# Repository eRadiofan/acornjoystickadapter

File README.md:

Joystick Adapter for Acorn Archimedes Computers
===============================================

KiCad project for an Archimedes joystick adapter. Derived from an initial design by **Ian Haylock** that plugs externally into the computers parallel port and enables two Atari style joysticks to be plugged in. Software must be installed on the Archimedes to recognize the adapter, see ``software`` folder. Full details and pictures can be found in this Stardot Forum [thread](https://stardot.org.uk/forums/viewtopic.php?f=16&t=24492). See ``release`` folder for latest version manufcatoring files along with a BOM file.

This fork contains some improvements by Radiofan, including shorter traces, adjustments for (slightly cheaper) connectors, use of 0805 resistors and through-hole capacitors (common stock).

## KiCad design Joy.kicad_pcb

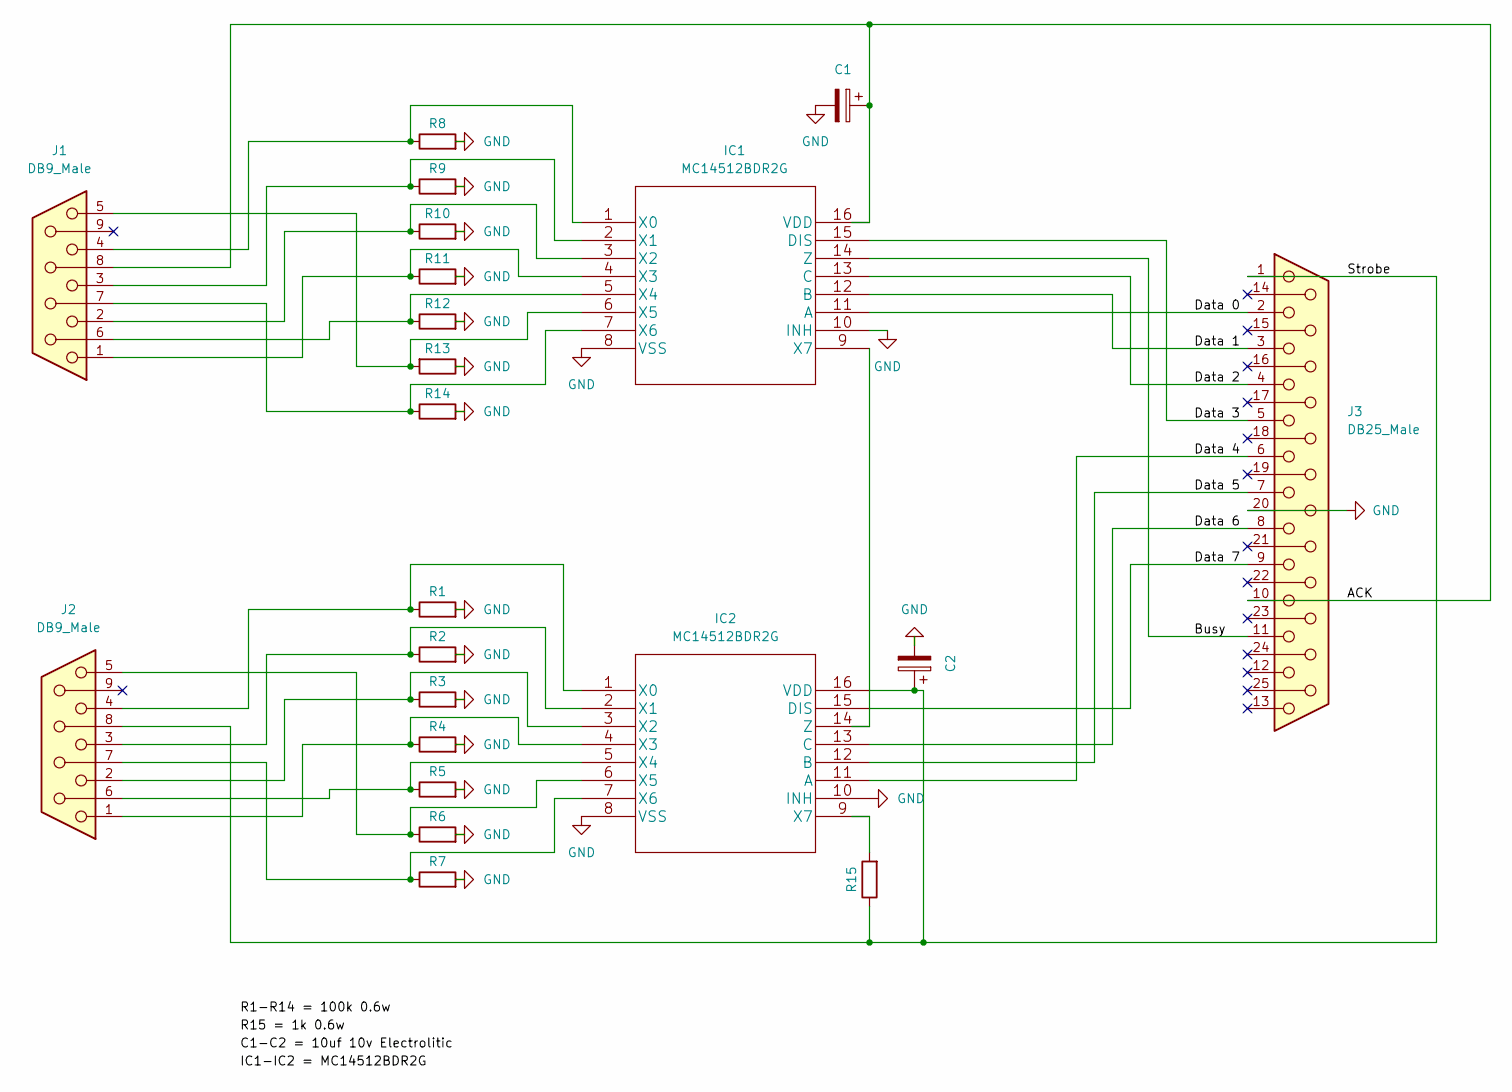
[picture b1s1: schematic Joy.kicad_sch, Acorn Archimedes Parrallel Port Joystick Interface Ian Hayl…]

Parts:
C1, C2: C_Polarized, 10uf Eletrolitic; CP_Radial_D5.0mm_P2.00mm
IC1, IC2: MC14512BDR2G; SOIC-16_3.9x9.9mm_P1.27mm
J1, J2: DB9_Male; 5747840-4
J3: DB25_Male; 5788794-1
R1, R2, R3, R4, R5, R6, R7, R8, R9, R10, R11, R12, R13, R14: 100k; R_0805_2012Metric_Pad1.20x1.40mm_HandSolder
R15: 1k; R_0805_2012Metric_Pad1.20x1.40mm_HandSolder

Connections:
/ACK: C1.1, IC1.16 (VDD), J1.8, J3.10
/Busy: IC1.14 (Z), J3.11
/Data 0: IC1.11 (A), J3.2
/Data 1: IC1.12 (B), J3.3
/Data 2: IC1.13 (C), J3.4
/Data 3: IC1.15 (DIS), J3.5
/Data 4: IC2.11 (A), J3.6
/Data 5: IC2.12 (B), J3.7
/Data 6: IC2.13 (C), J3.8
/Data 7: IC2.15 (DIS), J3.9
/Strobe: C2.1, IC2.16 (VDD), J2.8, J3.1, R15.1
GND: C1.2, C2.2, IC1.8 (VSS), IC1.10 (INH), IC2.8 (VSS), IC2.10 (INH), J3.20, R1.2, R2.2, R3.2, R4.2, R5.2, R6.2, R7.2, R8.2, R9.2, R10.2, R11.2, R12.2, R13.1, R14.2
unnamed: IC1.1 (X0), J1.4, R8.1
unnamed: IC1.2 (X1), J1.3, R9.1
unnamed: IC1.3 (X2), J1.2, R10.1
unnamed: IC1.4 (X3), J1.1, R11.1
unnamed: IC1.5 (X4), J1.6, R12.1
unnamed: IC1.6 (X5), J1.5, R13.2
unnamed: IC1.7 (X6), J1.7, R14.1
unnamed: IC1.9 (X7), IC2.14 (Z)
unnamed: IC2.1 (X0), J2.4, R1.1
unnamed: IC2.2 (X1), J2.3, R2.1
unnamed: IC2.3 (X2), J2.2, R3.1
unnamed: IC2.4 (X3), J2.1, R4.1
unnamed: IC2.5 (X4), J2.6, R5.1
unnamed: IC2.6 (X5), J2.5, R6.1
unnamed: IC2.7 (X6), J2.7, R7.1
unnamed: IC2.9 (X7), R15.2

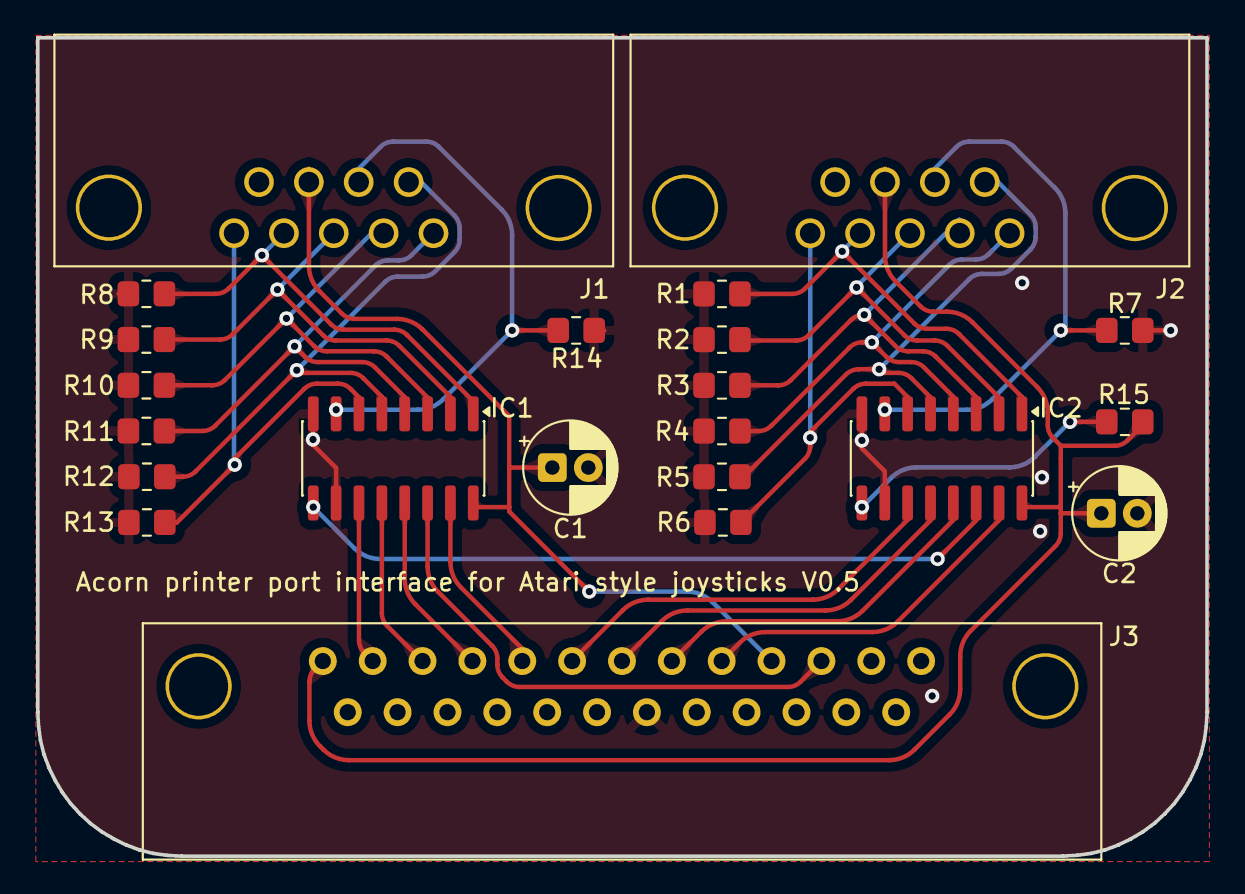
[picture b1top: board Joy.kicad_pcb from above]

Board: 2 copper layers, 65.0 x 45.5 mm, 22 parts (0 on the bottom side), 28 nets.

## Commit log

2025-12-09 Capacitors now through-hole, resistors 0805, cheaper connectors
2025-12-22 Updated module
